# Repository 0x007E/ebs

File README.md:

# `EBS` - Ethernally Blink Solar (Ewigblink)

The `EBS` project is based on a pcb with photodiodes ([PB333](#additional-information)) and a supercap ([HV0810](#additional-information)) with `1F` so that in combination with sunlight the state of the led starts changing.

| Experience | Level |
|:------------|:-----:|
| Soldering   |  |
| Mechanical  |  |

# Downloads

| Type      | File               | Description              |
|:---------:|:------------------:|:-------------------------|
| Simulation | [asc](https://github.com/0x007E/ebs/raw/refs/heads/main/EBS.asc) | LTSpice Simulation | 
| Lochmaster | [lm4](https://github.com/0x007E/ebs/raw/refs/heads/main/EBS.LM4) | Stripe grid circuit board | 
| Schematic | [pdf](https://github.com/0x007E/ebs/releases/latest/download/schematic.pdf) / [cadlab](https://cadlab.io/project/28595/main/files)     | Schematic files          |
| Board     | [pdf](https://github.com/0x007E/ebs/releases/latest/download/pcb.pdf) / [cadlab](https://cadlab.io/project/28595/main/files)     | Board file               |
| Drill     | [pdf](https://github.com/0x007E/ebs/releases/latest/download/drill.pdf) | Drill file               |
| PCB   | [zip](https://github.com/0x007E/ebs/releases/latest/download/kicad.zip) / [tar](https://github.com/0x007E/ebs/releases/latest/download/kicad.tar.gz)                | KiCAD/Gerber/BoM/Drill files       |
| Mechanical | [zip](https://github.com/0x007E/ebs/releases/latest/download/freecad.zip) / [tar](https://github.com/0x007E/ebs/releases/latest/download/freecad.tar.gz) | FreeCAD/Housing and PCB (STEP) files     |

# Hardware

There are two parts of the hardware. The pcb and the housing of the `EBS`. The pcb is created with `KiCAD` and the housing with `FreeCAD`. All files are built with `github actions` so that they are ready for a production environment. The housing is printed with a 3D-printer (`Dremel 3D40`).

## PCB

The circuit board is populated on one side (Top). The best way for soldering is within a standard soldering system.

### Top Layer

### Bottom Layer

## Mechanical

The housing has a tolerance of `0.2mm` on each side of the case. So the pcb should fit perfectly in the housing.

### Assembled

#### Exploded

# Additional Information

| Type       | Link               | Description              |
|:----------:|:------------------:|:-------------------------|
| PB333 | [pdf](https://www.everlighteurope.com/custom/files/datasheets/DPD-0000154.pdf) | Photodiode |
| HV0810 | [pdf](https://www.eaton.com/content/dam/eaton/products/electronic-components/resources/data-sheet/eaton-hv-supercapacitors-cylindrical-cells-data-sheet.pdf) | Supercap |)

---

R. GAECHTER

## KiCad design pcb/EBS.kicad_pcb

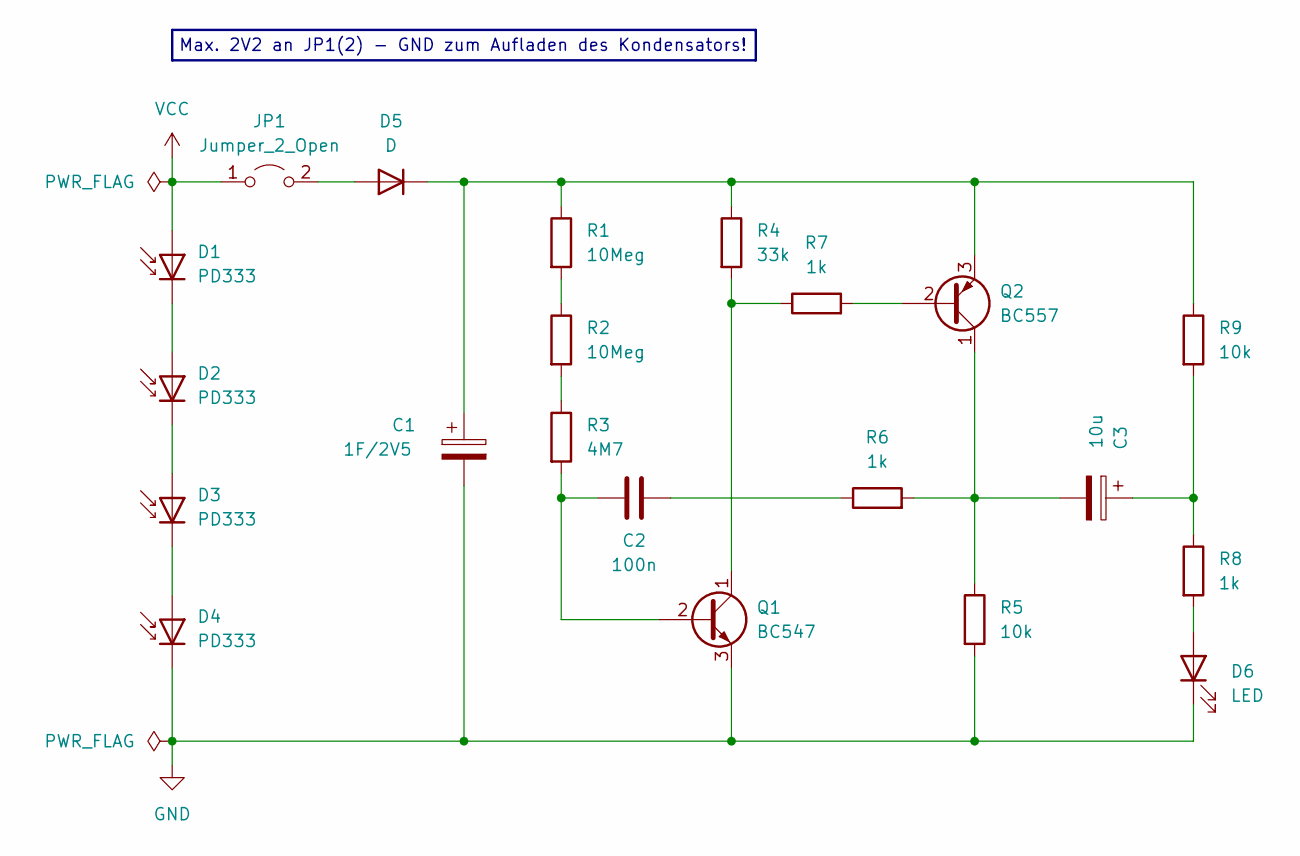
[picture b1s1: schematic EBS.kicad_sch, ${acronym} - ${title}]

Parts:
C1: 1F/2V5; CP_Radial_D6.3mm_P2.50mm
C2: 100n; C_Disc_D3.8mm_W2.6mm_P2.50mm
C3: 10u; CP_Radial_D5.0mm_P2.50mm
D1, D2, D3, D4: PD333; LED_D5.0mm
D5: D; D_A-405_P7.62mm_Horizontal
D6: LED; LED_D5.0mm
JP1: Jumper_2_Open; PinHeader_1x02_P2.54mm_Vertical
Q1: BC547; TO-92_Inline_Wide
Q2: BC557; TO-92_Inline_Wide
R1, R2: 10Meg; R_Axial_DIN0207_L6.3mm_D2.5mm_P10.16mm_Horizontal
R3: 4M7; R_Axial_DIN0207_L6.3mm_D2.5mm_P10.16mm_Horizontal
R4: 33k; R_Axial_DIN0207_L6.3mm_D2.5mm_P10.16mm_Horizontal
R5, R9: 10k; R_Axial_DIN0207_L6.3mm_D2.5mm_P10.16mm_Horizontal
R6, R7, R8: 1k; R_Axial_DIN0207_L6.3mm_D2.5mm_P10.16mm_Horizontal

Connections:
GND: C1.2, D4.1 (K), D6.1 (K), Q1.3 (E), R5.2
unnamed: C2.2, R6.1
unnamed: C3.1, R8.1, R9.2
unnamed: D1.1 (K), D2.2 (A)
unnamed: D2.1 (K), D3.2 (A)
unnamed: D3.1 (K), D4.2 (A)
unnamed: D5.2 (A), JP1.2 (B)
unnamed: C1.1, D5.1 (K), Q2.3 (E), R1.1, R4.1, R9.1
unnamed: D6.2 (A), R8.2
unnamed: C2.1, Q1.2 (B), R3.2
unnamed: Q1.1 (C), R4.2, R7.1
unnamed: Q2.2 (B), R7.2
unnamed: C3.2, Q2.1 (C), R5.1, R6.2
unnamed: R1.2, R2.1
unnamed: R2.2, R3.1
VCC: D1.2 (A), JP1.1 (A)

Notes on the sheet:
Max. 2V2 an JP1(2) - GND zum Aufladen des Kondensators!

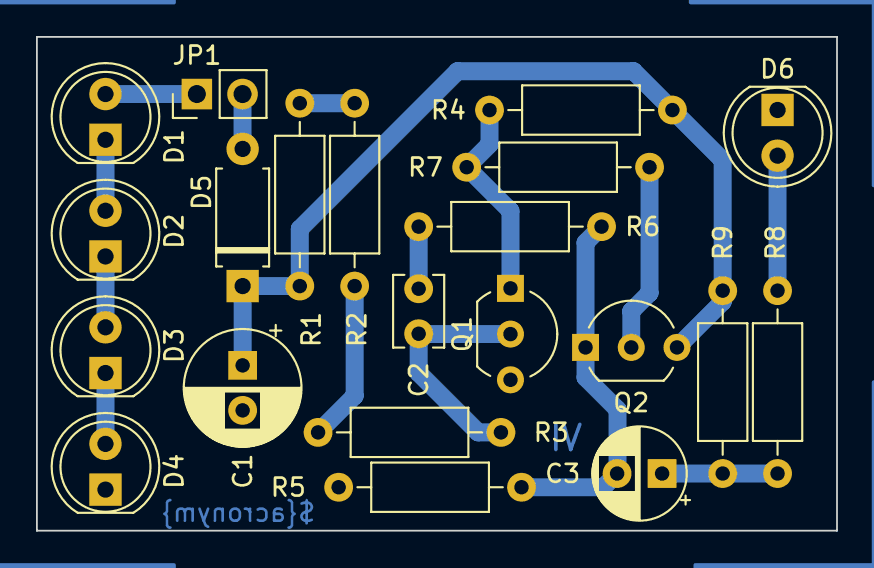
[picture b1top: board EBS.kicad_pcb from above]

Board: 2 copper layers, 44.4 x 27.4 mm, 21 parts (0 on the bottom side), 16 nets.

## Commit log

2024-10-24 Add README
2024-10-24 Create pipeline
2025-01-19 Add missing text and parts
2025-01-19 Add image for social preview
2025-01-19 Update freecad version
2025-01-19 Add value to BOM
2025-01-19 Fix command execution
2025-01-19 Increment freecad version
2025-01-19 Update images
2025-01-24 Corrector mirroring
2025-01-24 Fix path and explosion drawing
2025-01-24 Refresh images
2025-01-24 Add TechDraw
2025-01-24 Add housing to artifacts
2025-01-24 Move path
2025-01-24 Rename download parts
2025-02-21 Change pcb scaling for pdf
2025-04-09 Change resistor unit
2025-04-18 Add resistor options
2025-04-18 Extend information text
2025-04-18 Change 3d models
2025-04-18 Ignore footprint missmatch
2025-04-18 Change ferrule on leds
2025-04-18 Add jumper model to JP1
2025-04-18 Update 3d models on pcb
2025-04-18 Change led models
2025-04-18 Switch to updated led models
2025-04-18 Update preview image
2025-04-18 Disable visibility of trajectory line
2025-04-18 Fix BOM integration
2025-04-18 Optimize rendering light position

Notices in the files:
README.md:
License CC By-NC-SA
parts and their libraries:
license: CC BY-NC-SA 4.0
